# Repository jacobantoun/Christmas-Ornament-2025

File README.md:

# Jacob's Somewhat Yearly Christmas Ornament PCB

## About this Ornament
Each year I try to design a Christmas themed PCB and often get carried away trying to make them fancier than they need to be. This year I just stuck with creating a basic PCB with minimial functionality that's hard to mess up. I had a bunch of 3mm LEDs laying around and a couple sleeves of the Atmel (Microchip) ATTiny816 laying around waiting to be used.
The ornament makes use of the AVRs built in sleep functionality. I have ornaments from a few years ago that still have the original battery because of how good the sleep mode is.
## Build Pictures

## How to use
Press the button and the LEDs will do stuffs
## Programming
Source code can be found in the repo. The PCB contains a 2x3 pinheader for use with the Atmel ICE. The header is correct for the included 10 pin adapter cable. The PCB is also labeled with the appropriate UPDI pins.
## Building the Ornaments
Remind me next year to let JLCPCB assemble these... and to not use through-hole components. I wanted to save money by soldering the thru-hole components myself, but bending, placing, soldering, and snipping all the leads took forever. There is something satisfying about assembling these all myself though.

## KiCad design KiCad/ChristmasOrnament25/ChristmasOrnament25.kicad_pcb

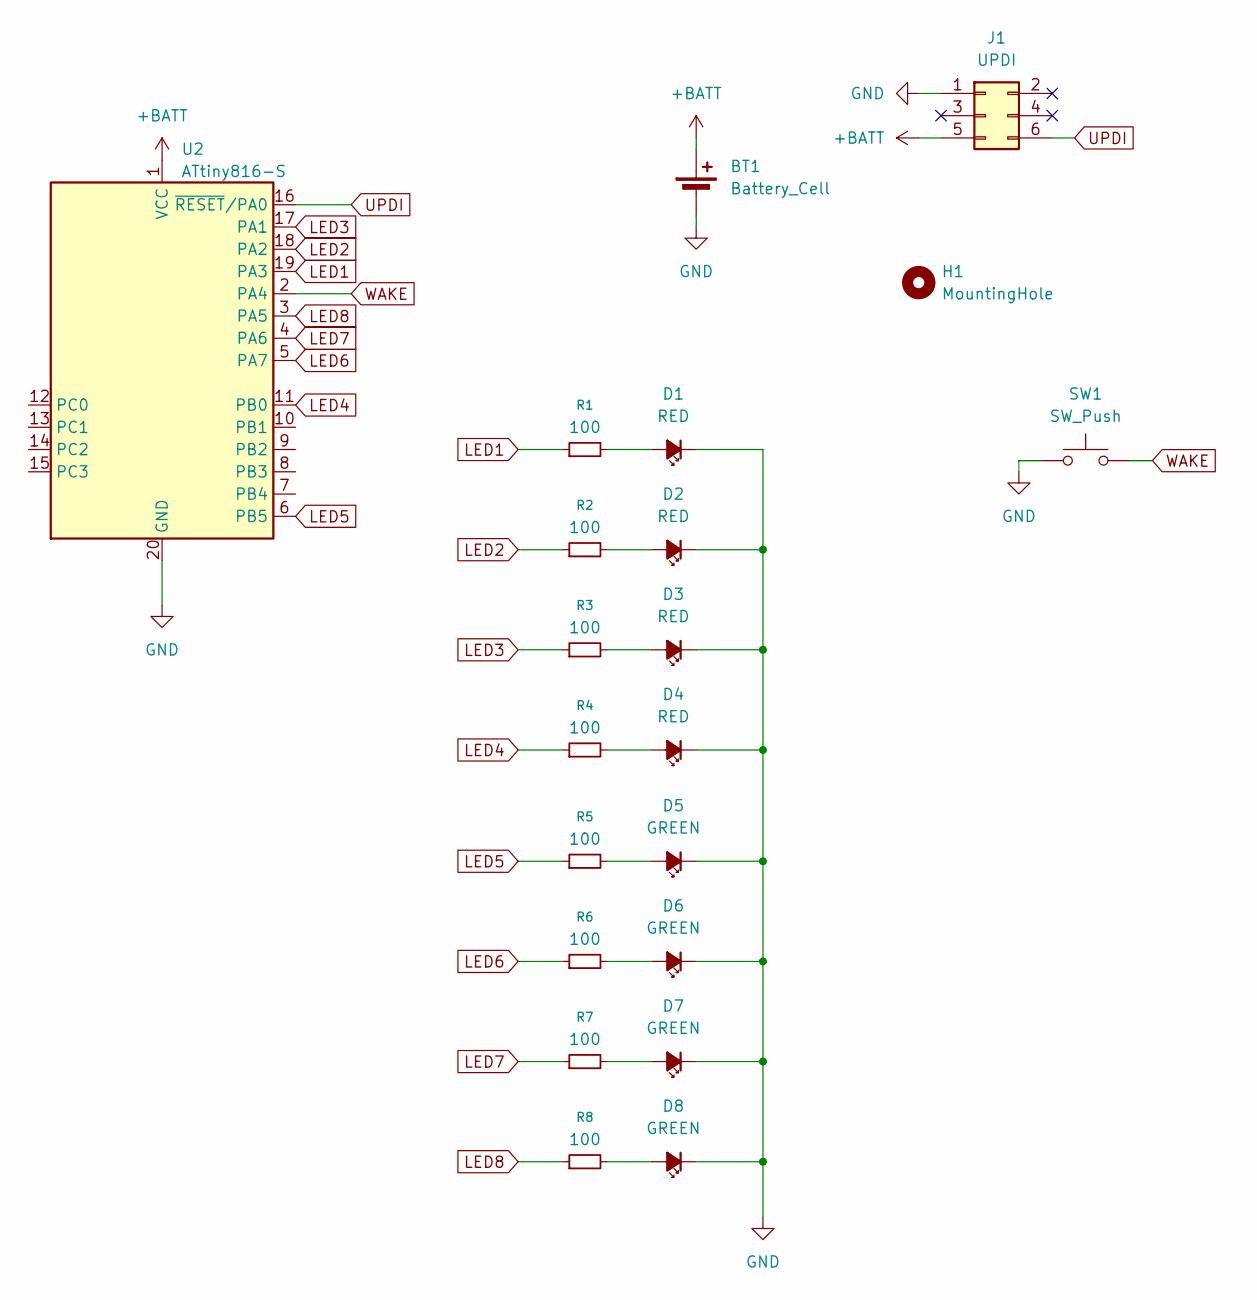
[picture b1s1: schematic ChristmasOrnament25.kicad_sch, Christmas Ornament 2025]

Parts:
BT1: Battery_Cell; BatteryHolder_Keystone_3002_1x2032; Manufacturer PN BAT-HLD-001-THM
D1, D2, D3, D4: RED; LED_D3.0mm
D5, D6, D7, D8: GREEN; LED_D3.0mm
H1: MountingHole; MountingHole_2.5mm
J1: UPDI; PinHeader_2x03_P2.54mm_Vertical; Manufacturer PN PR20203VBDN
R1, R2, R3, R4, R5, R6, R7, R8: 100; R_Axial_DIN0207_L6.3mm_D2.5mm_P7.62mm_Horizontal
SW1: SW_Push; SW_TH_Tactile_Omron_B3F-100x; Manufacturer PN B3F-1000
U2: ATtiny816-S; SOIC-20W_7.5x12.8mm_P1.27mm

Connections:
+BATT: BT1.1 (+), J1.5, U2.1 (VCC)
GND: BT1.2 (-), D1.1 (K), D2.1 (K), D3.1 (K), D4.1 (K), D5.1 (K), D6.1 (K), D7.1 (K), D8.1 (K), J1.1, SW1.1, U2.20 (GND)
LED1: R1.1, U2.19 (PA3)
LED2: R2.1, U2.18 (PA2)
LED3: R3.1, U2.17 (PA1)
LED4: R4.1, U2.11 (PB0)
LED5: R5.1, U2.6 (PB5)
LED6: R6.1, U2.5 (PA7)
LED7: R7.1, U2.4 (PA6)
LED8: R8.1, U2.3 (PA5)
unnamed: D1.2 (A), R1.2
unnamed: D2.2 (A), R2.2
unnamed: D3.2 (A), R3.2
unnamed: D4.2 (A), R4.2
unnamed: D5.2 (A), R5.2
unnamed: D6.2 (A), R6.2
unnamed: D7.2 (A), R7.2
unnamed: D8.2 (A), R8.2
UPDI: J1.6, U2.16 (~RESET/PA0)
WAKE: SW1.2, U2.2 (PA4)

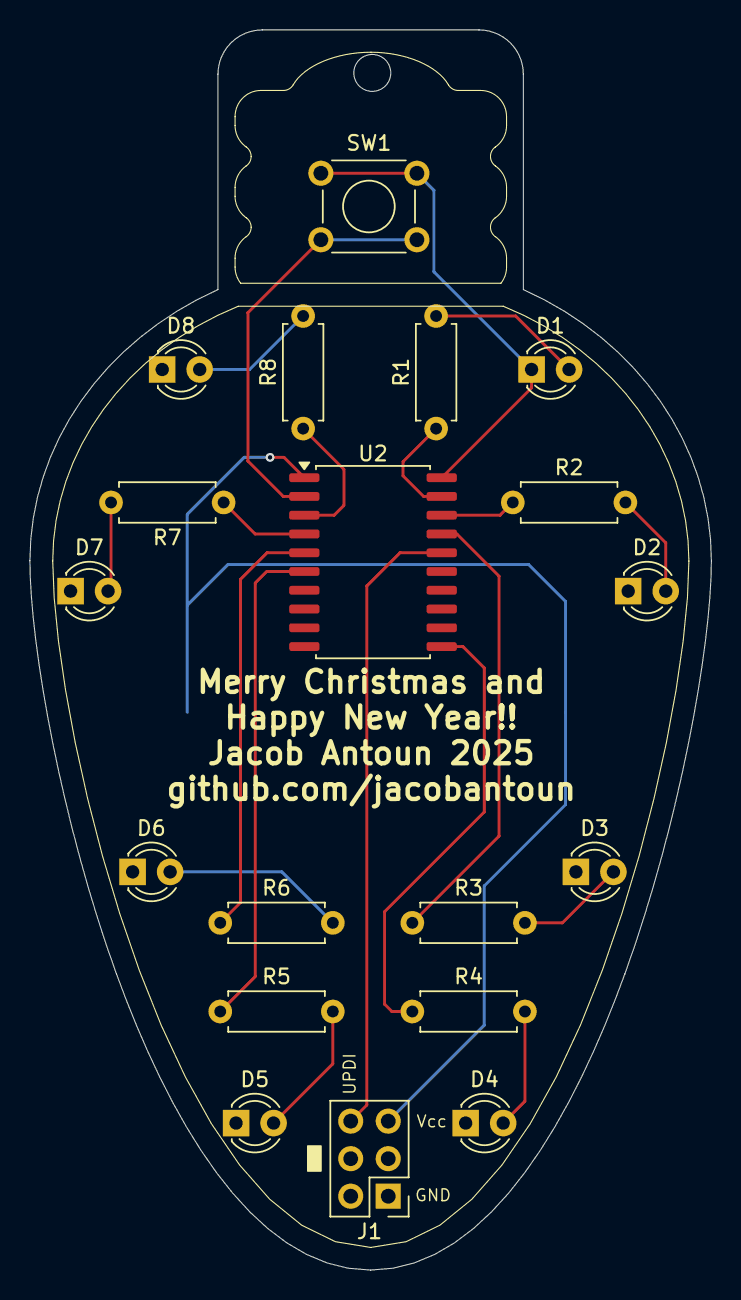
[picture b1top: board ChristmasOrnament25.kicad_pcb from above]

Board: 2 copper layers, 46.1 x 83.9 mm, 21 parts (1 on the bottom side), 20 nets.

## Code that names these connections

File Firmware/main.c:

#include <avr/io.h>
#include <util/delay.h>
#include <avr/interrupt.h>
#include <avr/sleep.h>
#include <stdlib.h>  // For rand()

#define CHASER_DELAY_TIME 500
#define TWINKLE_DELAY_TIME 100

// Function prototypes
void init_leds(void);
void led_on(uint8_t led_number);
void led_off(uint8_t led_number);
void all_leds_off(void);
void single_led_chaser_cw(uint8_t number_of_cycles);
void single_led_chaser_ccw(uint8_t number_of_cycles);
void double_led_chaser(uint8_t number_of_cycles);
void twinkling_stars(uint8_t cycles, uint16_t base_delay_ms);
void delay_millis(uint16_t ms);


// Function to blink the LED connected to PA5 five times
void blink_five_times(void) {
	for (uint8_t i = 0; i < 5; i++) {
		PORTA.OUTSET = (1 << 5);  
		_delay_ms(500);           
		PORTA.OUTCLR = (1 << 5);  
		_delay_ms(500);           
	}
}

// Interrupt Service Routine for PORTA
ISR(PORTA_PORT_vect) {
	PORTA.INTFLAGS = (1 << 4);  // Clear the interrupt flag for PA4
}

int main(void) {
	
    // Set LEDs as output
	init_leds();
    
	// Switch on PA4. Set as input, pull up enable, interrupt
	PORTA.DIRCLR = (1 << 4);
	PORTA.PIN4CTRL = PORT_PULLUPEN_bm | PORT_ISC_BOTHEDGES_gc;  // Enable pull-up and both-edges interrupt
	
	// Set the sleep mode to Power-Down for low power consumption
	set_sleep_mode(SLEEP_MODE_PWR_DOWN);
	
	// Perform the initial blinking sequence
	blink_five_times();
	
	// Main loop: Sleep, wake on interrupt, check pin state, blink if pressed, repeat
	while (1) {
		sleep_enable();      // Enable sleep mode
		sei();               // Enable global interrupts
		sleep_cpu();         // Enter sleep mode (wakes on interrupt)
		sleep_disable();     // Disable sleep mode after wake-up
		
		_delay_ms(10);       // Brief debounce delay
		
		// Check if the button is pressed
		if (!(PORTA.IN & (1 << 4))) {
			single_led_chaser_cw(2);
			_delay_ms(1000);
			single_led_chaser_ccw(2);
			all_leds_off();
			_delay_ms(500);
			twinkling_stars(15, 1000);
			
		}
	}
	
	return 0;
}

// Function to initialize all LED pins as outputs
void init_leds(void) 
{
	// Configure PORTA pins: PA3, PA2, PA1, PA7, PA6, PA5 as outputs
	PORTA.DIRSET = (1 << 3) | (1 << 2) | (1 << 1) | (1 << 7) | (1 << 6) | (1 << 5);
	
	// Configure PORTB pins: PB0, PB5 as outputs
	PORTB.DIRSET = (1 << 0) | (1 << 5);
}

// This functions turns a specific LED (D1 - D8) ON
void led_on(uint8_t led_number)
{
	if(led_number < 1 || led_number > 8)
	{
		return;
	}
	switch(led_number)
	{
		case 1: PORTA.OUTSET = (1 << 3); break;
		case 2: PORTA.OUTSET = (1 << 2); break;
		case 3: PORTA.OUTSET = (1 << 1); break;
		case 4: PORTB.OUTSET = (1 << 0); break;
		case 5: PORTB.OUTSET = (1 << 5); break;
		case 6: PORTA.OUTSET = (1 << 7); break;
		case 7: PORTA.OUTSET = (1 << 6); break;
		case 8: PORTA.OUTSET = (1 << 5); break;
	}
}

// This functions turns a specific LED (D1 - D8) OFF
void led_off(uint8_t led_number)
{
	if(led_number < 1 || led_number > 8)
	{
		return;
	}
	switch(led_number)
	{
		case 1: PORTA.OUTCLR = (1 << 3); break;
		case 2: PORTA.OUTCLR = (1 << 2); break;
		case 3: PORTA.OUTCLR = (1 << 1); break;
		case 4: PORTB.OUTCLR = (1 << 0); break;
		case 5: PORTB.OUTCLR = (1 << 5); break;
		case 6: PORTA.OUTCLR = (1 << 7); break;
		case 7: PORTA.OUTCLR = (1 << 6); break;
		case 8: PORTA.OUTCLR = (1 << 5); break;
	}
}

// Turns off all LEDs at once
void all_leds_off(void)
{
	PORTA.OUTCLR = (1 << 3) | (1 << 2) | (1 << 1) | (1 << 7) | (1 << 6) | (1 << 5);
	PORTB.OUTCLR = (1 << 0) | (1 << 5);
}

// Creates a small led "chaser". One LED is on and circling around the ornament clockwise
void single_led_chaser_cw(uint8_t number_of_cycles)
{
	for(uint8_t c = 0; c < number_of_cycles; c++)
	{
		for(uint8_t i = 1; i <= 8; i++)
		{
			all_leds_off();
			led_on(i);
			_delay_ms(CHASER_DELAY_TIME);
		}
	}
	all_leds_off();
}

// Function for single-LED chaser in a ring pattern (reverse direction)
void single_led_chaser_ccw(uint8_t number_of_cycles) 
{
	for (uint8_t c = 0; c < number_of_cycles; c++) {
		for (uint8_t i = 8; i >= 1; i--) {
			all_leds_off();       
			led_on(i);            
			_delay_ms(CHASER_DELAY_TIME);  
		}
	}
	all_leds_off();  
}

// Same as single_led_chaser() but with two LEDs instead of one.
void double_led_chaser(uint8_t number_of_cycles)
{
	for (uint8_t c = 0; c < number_of_cycles; c++) {
		for (uint8_t i = 1; i <= 8; i++) {
			all_leds_off();      
			led_on(i);           
			uint8_t next = (i % 8) + 1;  
			led_on(next);         
			_delay_ms(CHASER_DELAY_TIME);  
		}
	}
	all_leds_off();  // Ensure all off at end
}

// Revised twinkling stars function with variable delay support
void twinkling_stars(uint8_t cycles, uint16_t base_delay_ms) 
{
	srand(0xABCD);  // Seed random number generator 
	all_leds_off();
	for (uint8_t c = 0; c < cycles; c++) {
		uint8_t led = (rand() % 8) + 1;  // Select random LED from 1 to 8
		led_on(led);
		delay_millis(base_delay_ms + (rand() % 200));  // Variable delay
		led_off(led);
		_delay_ms(50);
	}
	all_leds_off();
}

void delay_millis(uint16_t ms)
{
	while(ms--)
	{
		_delay_ms(1);
	}
}

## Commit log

2025-12-22 Added KiCad files
2025-12-23 Added firmware
2025-12-23 Create ChristmasOrnament25.pdf Schematic
2025-12-23 Add build pictures to README
    Added build pictures to the README for visual reference.
2025-12-23 Add image to README for Christmas Ornament PCB
    Added an image to the README for better visual representation.
2025-12-23 Update section title for building ornaments
